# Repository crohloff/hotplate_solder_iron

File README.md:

# hotplate_solder_iron
SMD solder station based on old hot iron
inspired by [makermoekoe](https://github.com/makermoekoe/Hotplate-Soldering-Iron)

## HW BOM
- old hot iron
- 230V/5V power supply
- SSR-25 DA
- 10k potentiometer (through hole)
- 10k resistor (0805 SMD)
- button / PTS645 or similar (SMD)
- 0,96" OLED (SSD1306/1305)
- MAX6675 HW-550 (k-type)

## FW req
- arduino software
- U8g2 lib by oliver
- MAX6675 lib by Adafruit

## control board front

## control board back

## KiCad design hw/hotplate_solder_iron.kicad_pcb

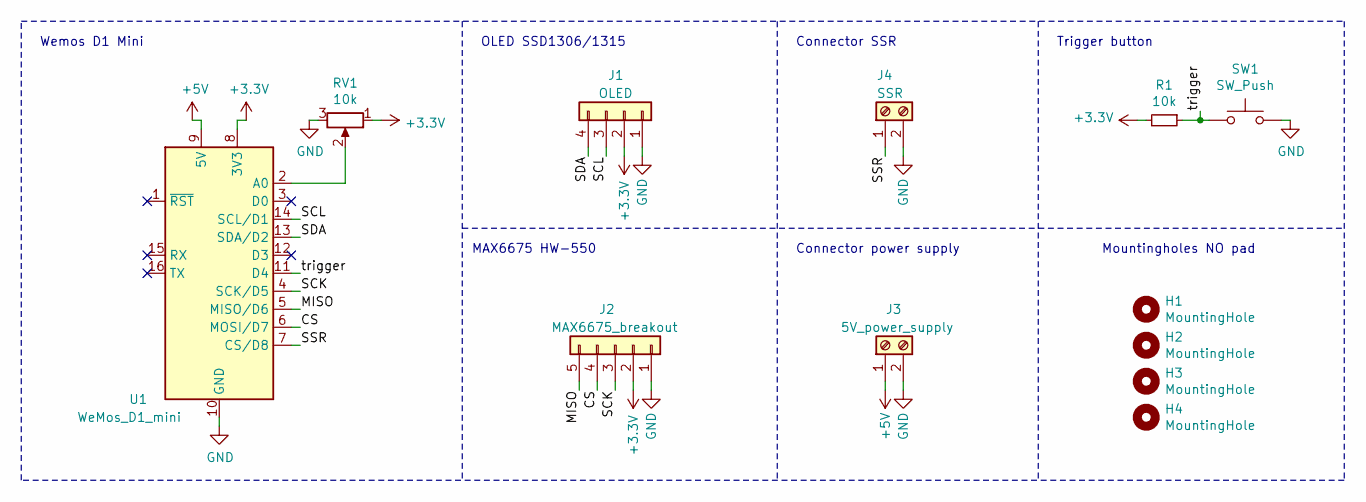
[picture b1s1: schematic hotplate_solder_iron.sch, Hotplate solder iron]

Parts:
H1, H2, H3, H4: MountingHole; MountingHole_3.2mm_M3
J1: OLED; PinHeader_1x04_P2.54mm_Vertical
J2: MAX6675_breakout; PinHeader_1x05_P2.54mm_Vertical
J3: 5V_power_supply; TerminalBlock_Altech_AK300-2_P5.00mm
J4: SSR; TerminalBlock_Altech_AK300-2_P5.00mm
R1: 10k; R_0805_2012Metric
RV1: 10k; Potentiometer_Alpha_RD901F-40-00D_Single_Vertical
SW1: SW_Push; SW_SPST_PTS645
U1: WeMos_D1_mini; WEMOS_D1_mini_light

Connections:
+3V3: J1.2, J2.2, R1.2, RV1.1, U1.8 (3V3)
+5V: J3.1, U1.9 (5V)
/CS: J2.4, U1.6 (MOSI/D7)
/MISO: J2.5, U1.5 (MISO/D6)
/SCK: J2.3, U1.4 (SCK/D5)
/SCL: J1.3, U1.14 (SCL/D1)
/SDA: J1.4, U1.13 (SDA/D2)
/SSR: J4.1, U1.7 (CS/D8)
/trigger: R1.1, SW1.1, U1.11 (D4)
GND: J1.1, J2.1, J3.2, J4.2, RV1.3, SW1.2, U1.10 (GND)
unnamed: RV1.2, U1.2 (A0)

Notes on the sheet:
MAX6675 HW-550
OLED SSD1306/1315
Wemos D1 Mini
Trigger button
Connector SSR
Connector power supply
Mountingholes NO pad

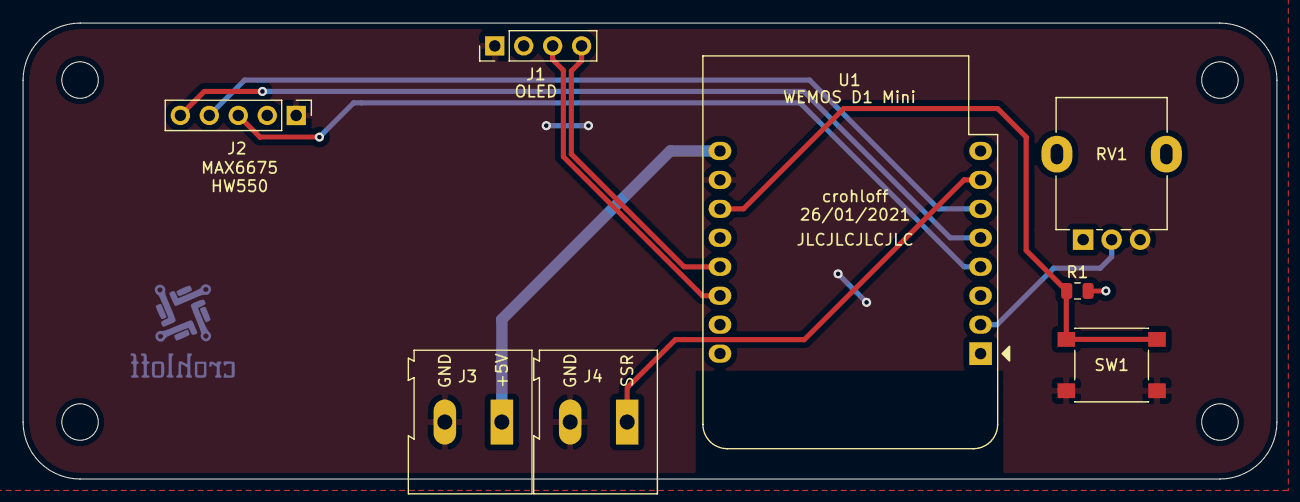
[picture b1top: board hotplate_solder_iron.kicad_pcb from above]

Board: 2 copper layers, 110.0 x 40.0 mm, 12 parts (0 on the bottom side), 11 nets.

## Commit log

2021-01-26 init
2021-05-13 adjust offset and temp regulation
